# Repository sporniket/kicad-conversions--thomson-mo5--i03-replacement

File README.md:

# Replacement of I03 (color PROM) for the Thomson MO5

> [WARNING] Please read carefully this note before using this project. It contains important facts.

Content

1. What is **Replacement of I03 (color PROM) for the Thomson MO5**, and when to use it ?
2. What should you know before using **Replacement of I03 (color PROM) for the Thomson MO5** ?
3. How to use **Replacement of I03 (color PROM) for the Thomson MO5** ?
4. Known issues
5. Miscellanous

## 1. What is **Replacement of I03 (color PROM) for the Thomson MO5**, and when to use it ?

**Replacement of I03 (color PROM) for the Thomson MO5** replaces the PROM that is used to convert pixel colors represented as a 4 bits value (pastel, red, green, blue) and a supplemental bit for blanking signal, into a RGB-222 value and a supplemental trigger signal for the builtin analog video incrustation feature (requires a specific extension) of the Thomson MO5.

### Licence

**Replacement of I03 (color PROM) for the Thomson MO5** is published under the Creative Commons CC0 license. You can find a copy of the licence there : https://creativecommons.org/publicdomain/zero/1.0/legalcode

You can copy, modify, distribute and perform the work, even for commercial purposes, all without asking permission.

**Replacement of I03 (color PROM) for the Thomson MO5** is distributed in the hope that it will be useful, but WITHOUT ANY WARRANTY; without even the implied warranty of MERCHANTABILITY or FITNESS FOR A PARTICULAR PURPOSE.

### Release notes

#### Release v2.0.0

* Resolves #6 : Add a breakout connector with R[1..2], V[1..2] and B[1..2] for adding custom DAC mods

Contains schematics in PDF files, gerber archive, and the JED file.

#### Release v1.0.0

Contains schematics in PDF files, gerber archive, and the JED file.

#### Release v1.0.0-rc1

**Hardware only** 

Contains schematics in PDF files, and gerber archive.

## 2. What should you know before using **Replacement of I03 (color PROM) for the Thomson MO5** ?

**Replacement of I03 (color PROM) for the Thomson MO5** is made of an hardware part to hold a GAL16v8 (or its current available compatible component ATF16v8) hereafter called "GAL", and a fusemap to be flashed onto said GAL.

* The hardware part is a Kicad 8 project describing the adapter from original chip socket in the computer motherboard
* The fusemap part is a source to be compiled by relevant tool to obtain a suitable JED fusemap.

> Do not use **Replacement of I03 (color PROM) for the Thomson MO5** if this project is not suitable for your project.

## 3. How to use **Replacement of I03 (color PROM) for the Thomson MO5** ?

### From sources

To get the latest available work, one must clone the git repository.

	git clone --recurse-submodules https://github.com/sporniket/kicad-conversions--thomson-mo5--i03-replacement.git

Then, open the project with Kicad 8.

To produce the fusemap... TO BE WRITTEN

## 4. Known issues
See the [project issues](https://github.com/sporniket/kicad-conversions--thomson-mo5--i03-replacement/issues) page.

## 5. Miscellanous

### Report issues
Use the [project issues](https://github.com/sporniket/kicad-conversions--thomson-mo5--i03-replacement/issues) page.

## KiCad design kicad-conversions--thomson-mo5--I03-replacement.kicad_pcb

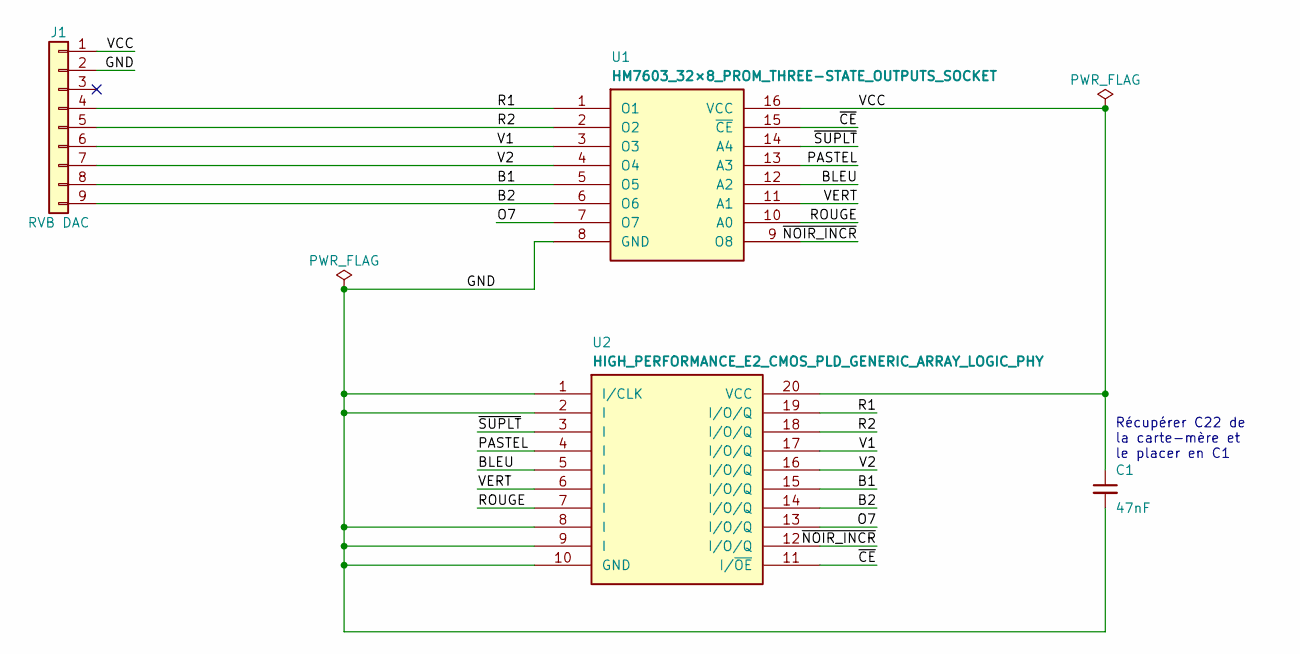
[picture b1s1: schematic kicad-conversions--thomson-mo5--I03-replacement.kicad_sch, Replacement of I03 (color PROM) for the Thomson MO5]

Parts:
C1: 47nF; Passive_THT_capacitor_mlcc_W2.54mm_L5.08mm
J1: RVB DAC; PinHeader_1x09_P2.54mm_Vertical
U1: HM7603_32×8_PROM_THREE-STATE_OUTPUTS_SOCKET; DIP-16_W7.62mm_LongPads
U2: HIGH_PERFORMANCE_E2_CMOS_PLD_GENERIC_ARRAY_LOGIC_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; DIP-20_W7.62mm_LongPads

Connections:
/B1: J1.8, U1.5 (O5), U2.15 (I/O/Q)
/B2: J1.9, U1.6 (O6), U2.14 (I/O/Q)
/BLEU: U1.12 (A2), U2.5 (I)
/GND: C1.2, J1.2, U1.8 (GND), U2.1 (I/CLK), U2.2 (I), U2.8 (I), U2.9 (I), U2.10 (GND)
/O7: U1.7 (O7), U2.13 (I/O/Q)
/PASTEL: U1.13 (A3), U2.4 (I)
/R1: J1.4, U1.1 (O1), U2.19 (I/O/Q)
/R2: J1.5, U1.2 (O2), U2.18 (I/O/Q)
/ROUGE: U1.10 (A0), U2.7 (I)
/V1: J1.6, U1.3 (O3), U2.17 (I/O/Q)
/V2: J1.7, U1.4 (O4), U2.16 (I/O/Q)
/VCC: C1.1, J1.1, U1.16 (VCC), U2.20 (VCC)
/VERT: U1.11 (A1), U2.6 (I)
/~CE: U1.15 (~CE), U2.11 (I/~OE)
/~NOIR_INCR: U1.9 (O8), U2.12 (I/O/Q)
/~SUPLT: U1.14 (A4), U2.3 (I)

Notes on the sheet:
Récupérer C22 de la carte-mère et le placer en C1

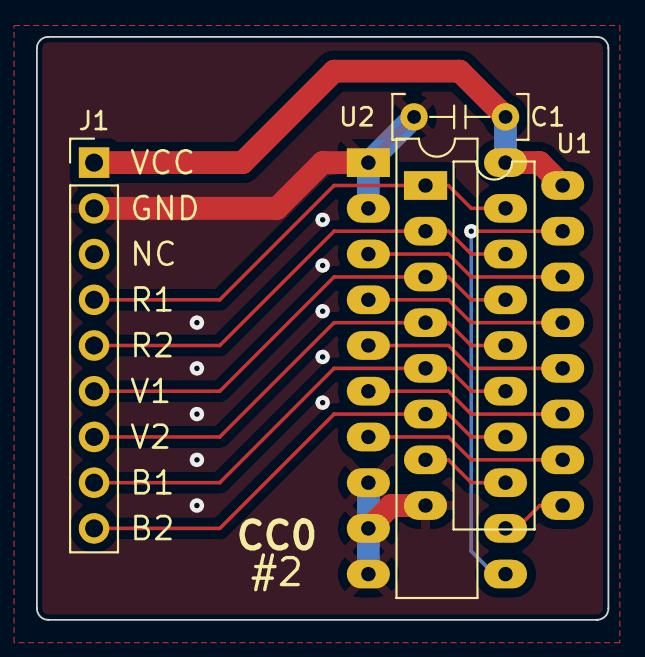
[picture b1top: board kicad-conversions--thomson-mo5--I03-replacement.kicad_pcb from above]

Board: 2 copper layers, 31.8 x 32.4 mm, 4 parts (0 on the bottom side), 16 nets.

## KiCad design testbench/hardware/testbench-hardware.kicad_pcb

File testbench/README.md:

# Testbench

The testbench allows to get data from an existing PROM, as well as checking data emitted by the replacement. Based on **Arduino Nano**, it consists of a hardware project, and a firmware project.

Design goals :

* a ZIF socket to swap devices under test
* The power supply of the device under test can be switched off ; the Arduino nano receives the switch command and enable/disable the power accordingly. It allows to swap devices without unplugging the testbench.
* Another switch for an "Automatic/Manual" mode.
* A push button to trigger an action that depends on the mode.
* Some LEDs to display :
  * whether the power supply of the device under test is on or off.
  * the address probed by the Arduino.
  * the data output of the device.
* The Arduino Nano send to the serial link the data read from the device under test, and display an OK/KO status with the onboard LED.

## Hardware project

**The schematic** is enough to build a device using prototype boards, or even breadboard, as I did. I have used a normal PNP transistor (rated with 500mA) from my parts box. Your mileage may vary.

**A pcb** is provided for convenience, it is not tested, but should be operationnal.

One particular parts for this PCB, selected because I have a lot of spares : the switches are [G-Switch SS-22F12-G060](https://www.lcsc.com/product-detail/Slide-Switches_G-Switch-SS-22F12-G060_C2848906.html)

The ZIF socket may be directly soldered, or plugged in a standard narrow DIP-16 socket, for easier servicing or recycling of this part.

## Firmware project

For now the implemented feature are :

* The power supply of the device under test can be switched on/off using the corresponding switch
* The address are probed continuously and the data is output to the serial. Open the serial monitor of the Arduino IDE to get the report.

That was enough to complete the main project.

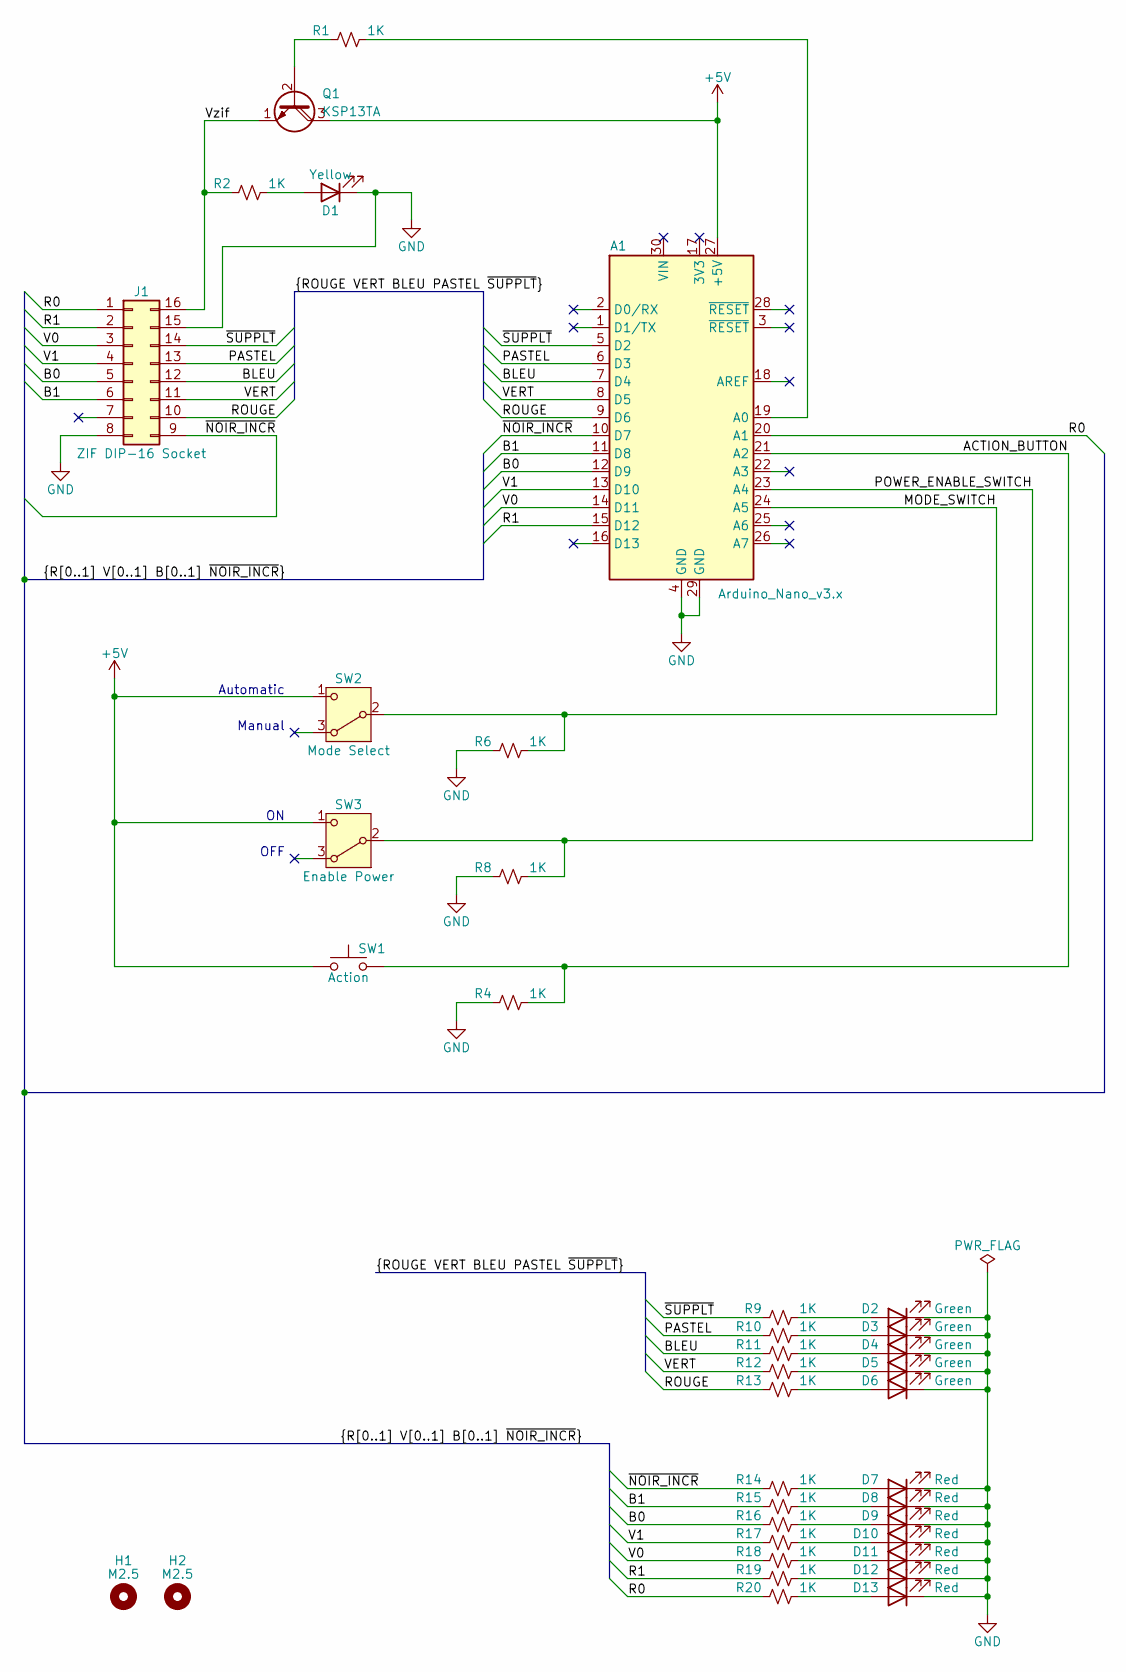
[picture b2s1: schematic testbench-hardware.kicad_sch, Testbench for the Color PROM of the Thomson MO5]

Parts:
A1: Arduino_Nano_v3.x; Arduino_Nano
D1: Yellow; LED_D3.0mm
D2, D3, D4, D5, D6: Green; LED_D3.0mm
D7, D8, D9, D10, D11, D12, D13: Red; LED_D3.0mm
H1, H2: M2.5; MountingHole_2.7mm_M2.5
J1: ZIF DIP-16 Socket; DIP-16_W7.62mm_Socket
Q1: KSP13TA; TO-92_Inline_Wide
R1, R2, R4, R6, R8, R9, R10, R11, R12, R13, R14, R15, R16, R17, R18, R19, R20: 1K; Passive_THT_resistor_W2.54mm_L12.70mm
SW1: Action; SW_PUSH-12mm
SW2: Mode Select; g-switch_22f12-gxxx--SPDT
SW3: Enable Power; g-switch_22f12-gxxx--SPDT

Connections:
+5V: A1.27 (+5V), Q1.3 (C), SW1.1, SW2.1 (C), SW3.1 (C)
/ACTION_BUTTON: A1.21 (A2), R4.2, SW1.2
/B0: A1.12 (D9), J1.5, R16.1
/B1: A1.11 (D8), J1.6, R15.1
/BLEU: A1.7 (D4), J1.12, R11.1
/MODE_SWITCH: A1.24 (A5), R6.2, SW2.2 (B)
/PASTEL: A1.6 (D3), J1.13, R10.1
/POWER_ENABLE_SWITCH: A1.23 (A4), R8.2, SW3.2 (B)
/R0: A1.20 (A1), J1.1, R20.1
/R1: A1.15 (D12), J1.2, R19.1
/ROUGE: A1.9 (D6), J1.10, R13.1
/V0: A1.14 (D11), J1.3, R18.1
/V1: A1.13 (D10), J1.4, R17.1
/VERT: A1.8 (D5), J1.11, R12.1
/Vzif: J1.16, Q1.1 (E), R2.1
/~NOIR_INCR: A1.10 (D7), J1.9, R14.1
/~SUPPLT: A1.5 (D2), J1.14, R9.1
GND: A1.4 (GND), A1.29 (GND), D1.1 (K), D2.1 (K), D3.1 (K), D4.1 (K), D5.1 (K), D6.1 (K), D7.1 (K), D8.1 (K), D9.1 (K), D10.1 (K), D11.1 (K), D12.1 (K), D13.1 (K), J1.8, J1.15, R4.1, R6.1, R8.1
unnamed: A1.19 (A0), R1.2
unnamed: D1.2 (A), R2.2
unnamed: D2.2 (A), R9.2
unnamed: D3.2 (A), R10.2
unnamed: D4.2 (A), R11.2
unnamed: D5.2 (A), R12.2
unnamed: D6.2 (A), R13.2
unnamed: D7.2 (A), R14.2
unnamed: D8.2 (A), R15.2
unnamed: D9.2 (A), R16.2
unnamed: D10.2 (A), R17.2
unnamed: D11.2 (A), R18.2
unnamed: D12.2 (A), R19.2
unnamed: D13.2 (A), R20.2
unnamed: Q1.2 (B), R1.1

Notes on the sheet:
Automatic
Manual
OFF

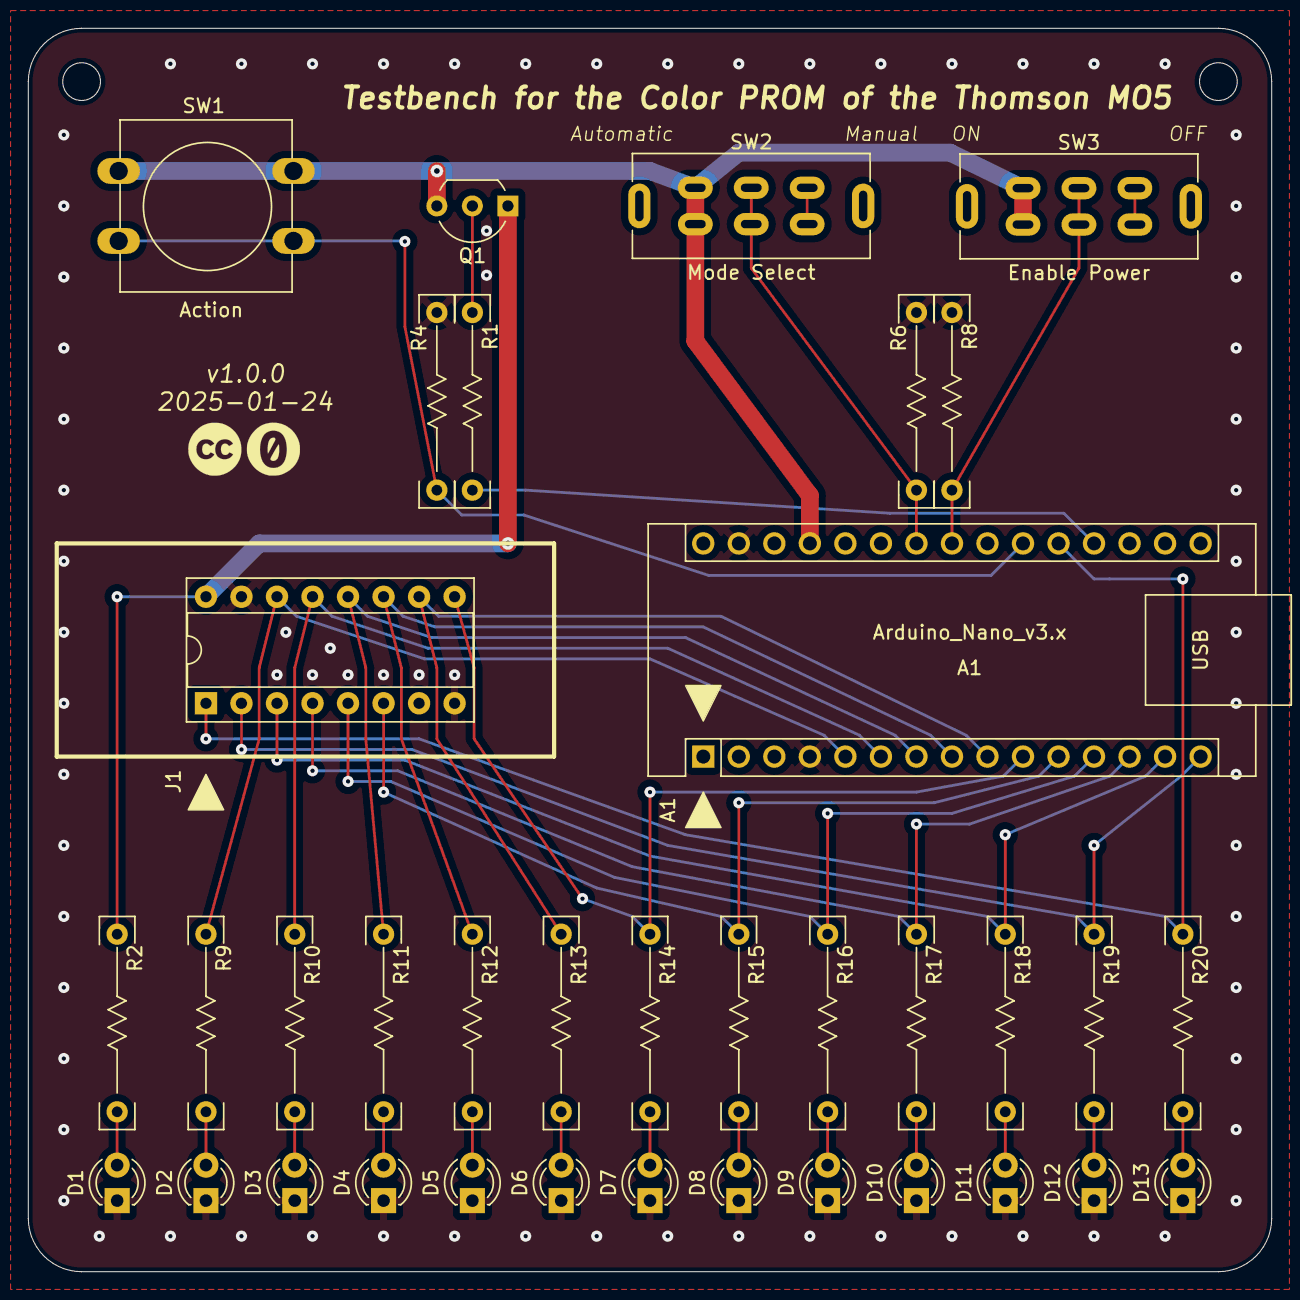
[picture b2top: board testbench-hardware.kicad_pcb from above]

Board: 2 copper layers, 88.9 x 88.9 mm, 38 parts (0 on the bottom side), 33 nets.

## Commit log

2024-11-03 done schematic
2024-11-03 reference my self-made footprints
2024-11-03 assign footprint to capacitor
2024-11-03 import pcb settings from main board
2024-11-03 done wiring
2024-11-03 final adjustments
2024-11-04 schematic -- rename wires with functionnal names
2024-11-09 readme and license
2024-11-09 drafts of fusemap description
2024-11-09 added proper description in schematic, pcb
2024-11-09 export release files
2024-11-09 prepare release -- README
2024-12-06 Ignore courtyard overlap
2024-12-06 testbench -- hardware schematic
2024-12-06 [testbench] no ERC violations
2024-12-06 [testbench] pcb layout
2024-12-07 [testbench] start wiring
2024-12-07 [testbench] done wiring
2024-12-07 [testbench] labels, cc-0 logos, tweak routing
2024-12-08 [testbench] started firmware
2024-12-09 [testbench] mounting holes
2024-12-09 [testbench] labels and marking adjustments
2024-12-10 [testbench] uses DPDT switches as SPDT switches for nicer routing
2025-01-02 [testbench] firmware just cycle through addresses and emit report
2025-01-17 [testbench] fixes bugs, impact of #2, better report
2025-01-17 [fusemap] refactor, and rework logic
2025-01-17 [fusemap] reworked green logic
2025-01-17 [fusemap] reworked red logic
2025-01-17 [fusemap] fixed typos
2025-01-18 [fusemap] fixed prom.pld, the problem was a wrong mapping for input pins
2025-01-20 Fixes #2 : [bug][testbench][hardware] A6 and A7 cannot be used as digital input
2025-01-20 [testbench][hardware] Tweaked the layout of some traces
2025-01-20 Fixes #3 : [bug][testbench] remove R3, R5 and R7
2025-01-21 Resolves #5 : [testbench][hardware] Change Q1 to a Darlington
2025-01-22 Fixes #4 : [bug][testbench][firmware] A6 and A7 cannot be used as digital input
2025-01-22 [testbench][firmware] Start refactoring -- extract phase management
2025-01-22 [testbench][firmware] format source + add readme to remind how to do it
2025-01-23 [testbench][firmware] refactor onboard led management
2025-01-23 [testbench][firmware] neater (column alignment) report lines
2025-01-23 [testbench][firmware] Refactor report generation and output
2025-01-23 [testbench][firmware] Refactor gpio driver for address
2025-01-23 [testbench][firmware] Refactor gpio driver for data
2025-01-23 [testbench][firmware] move all includes to the top
2025-01-24 [testbench][hardware] bump version and revision date
2025-01-24 [testbench][hardware] change position of R1, R4, R6, R8 for nicer traces
2025-01-24 [testbench] Add readme
2025-01-24 [testbench] move the gallery
2025-01-24 [testbench] tweaks readme
2025-01-25 prepare release : readme, date and rev of kicad files
2025-01-25 added a picture of the actual replacement installed on the motherboard
2025-01-25 add datasheets for reference
2025-07-27 Resolves #6 : Add a breakout connector with R[1..2], V[1..2] and B[1..2] for adding custom DAC mods
2025-07-27 prepare next release
